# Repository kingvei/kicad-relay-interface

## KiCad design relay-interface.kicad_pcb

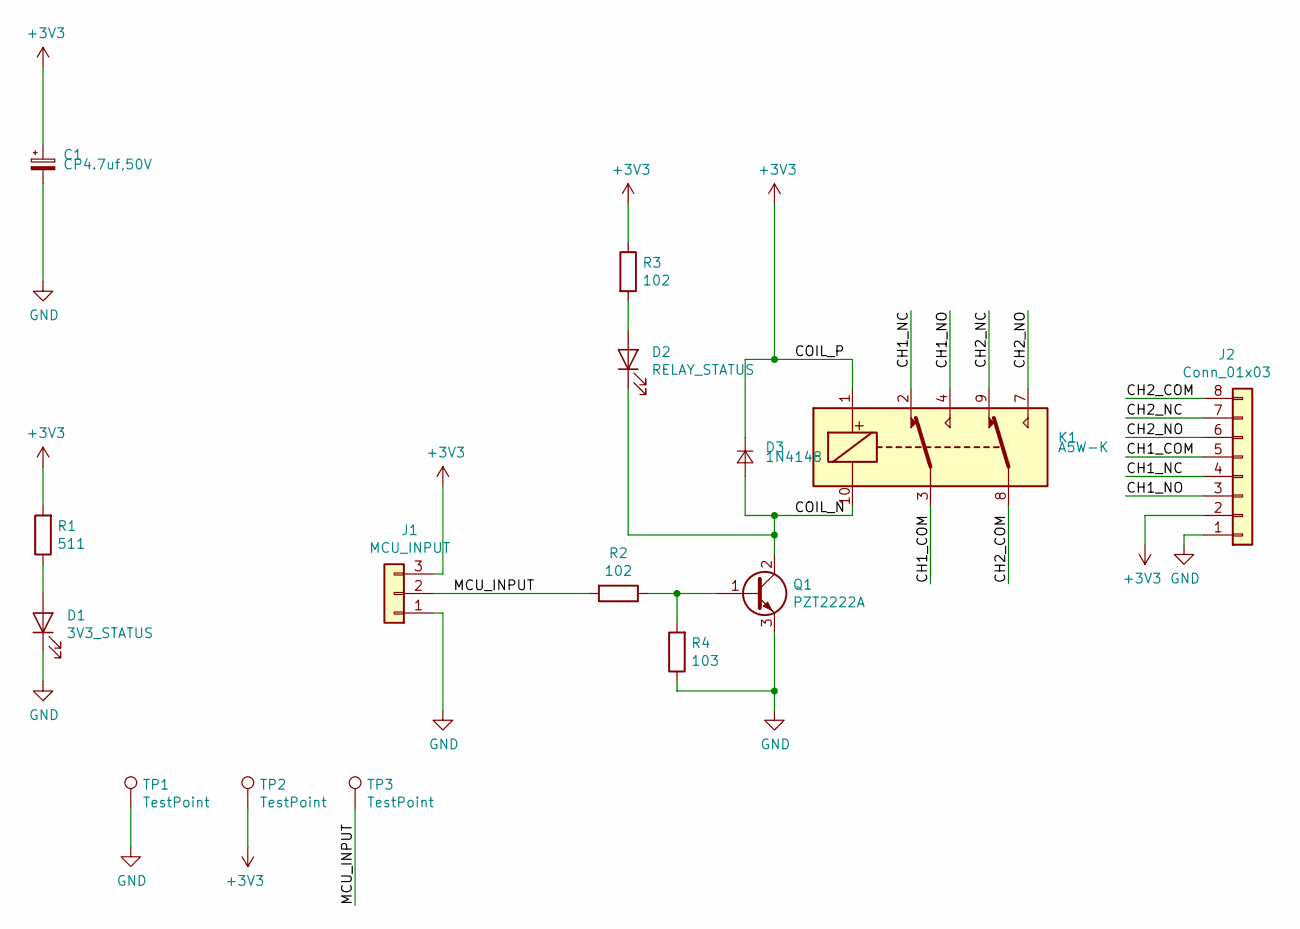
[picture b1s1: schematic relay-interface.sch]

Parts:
C1: CP4.7uf,50V; CP_Elec_4x5.3
D1: 3V3_STATUS; LED_0805_2012Metric_Castellated
D2: RELAY_STATUS; LED_0805_2012Metric_Castellated
D3: 1N4148; D_SOD-323_HandSoldering
J1: MCU_INPUT; PinHeader_1x03_P2.54mm_Vertical
J2: Conn_01x03; KF141V141R_Straight_1x08_Pitch2.54mm
K1: A5W-K; DIP-10_W7.62mm_LongPads
Q1: PZT2222A; SOT-223
R1: 511; R_0805_2012Metric_Pad1.15x1.40mm_HandSolder
R2, R3: 102; R_0805_2012Metric_Pad1.15x1.40mm_HandSolder
R4: 103; R_0805_2012Metric_Pad1.15x1.40mm_HandSolder
TP1, TP2, TP3: TestPoint; TestPoint_Pad_D2.0mm

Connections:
+3V3: C1.1, D3.1 (K), J1.3, J2.2, K1.1, R1.2, R3.1, TP2.1
/CH1_COM: J2.5, K1.3
/CH1_NC: J2.4, K1.2
/CH1_NO: J2.3, K1.4
/CH2_COM: J2.8, K1.8
/CH2_NC: J2.7, K1.9
/CH2_NO: J2.6, K1.7
/COIL_N: D2.1 (K), D3.2 (A), K1.10, Q1.2 (C)
/MCU_INPUT: J1.2, R2.2, TP3.1
GND: C1.2, D1.1 (K), J1.1, J2.1, Q1.3 (E), R4.1, TP1.1
unnamed: D1.2 (A), R1.1
unnamed: D2.2 (A), R3.2
unnamed: Q1.1 (B), R2.1, R4.2

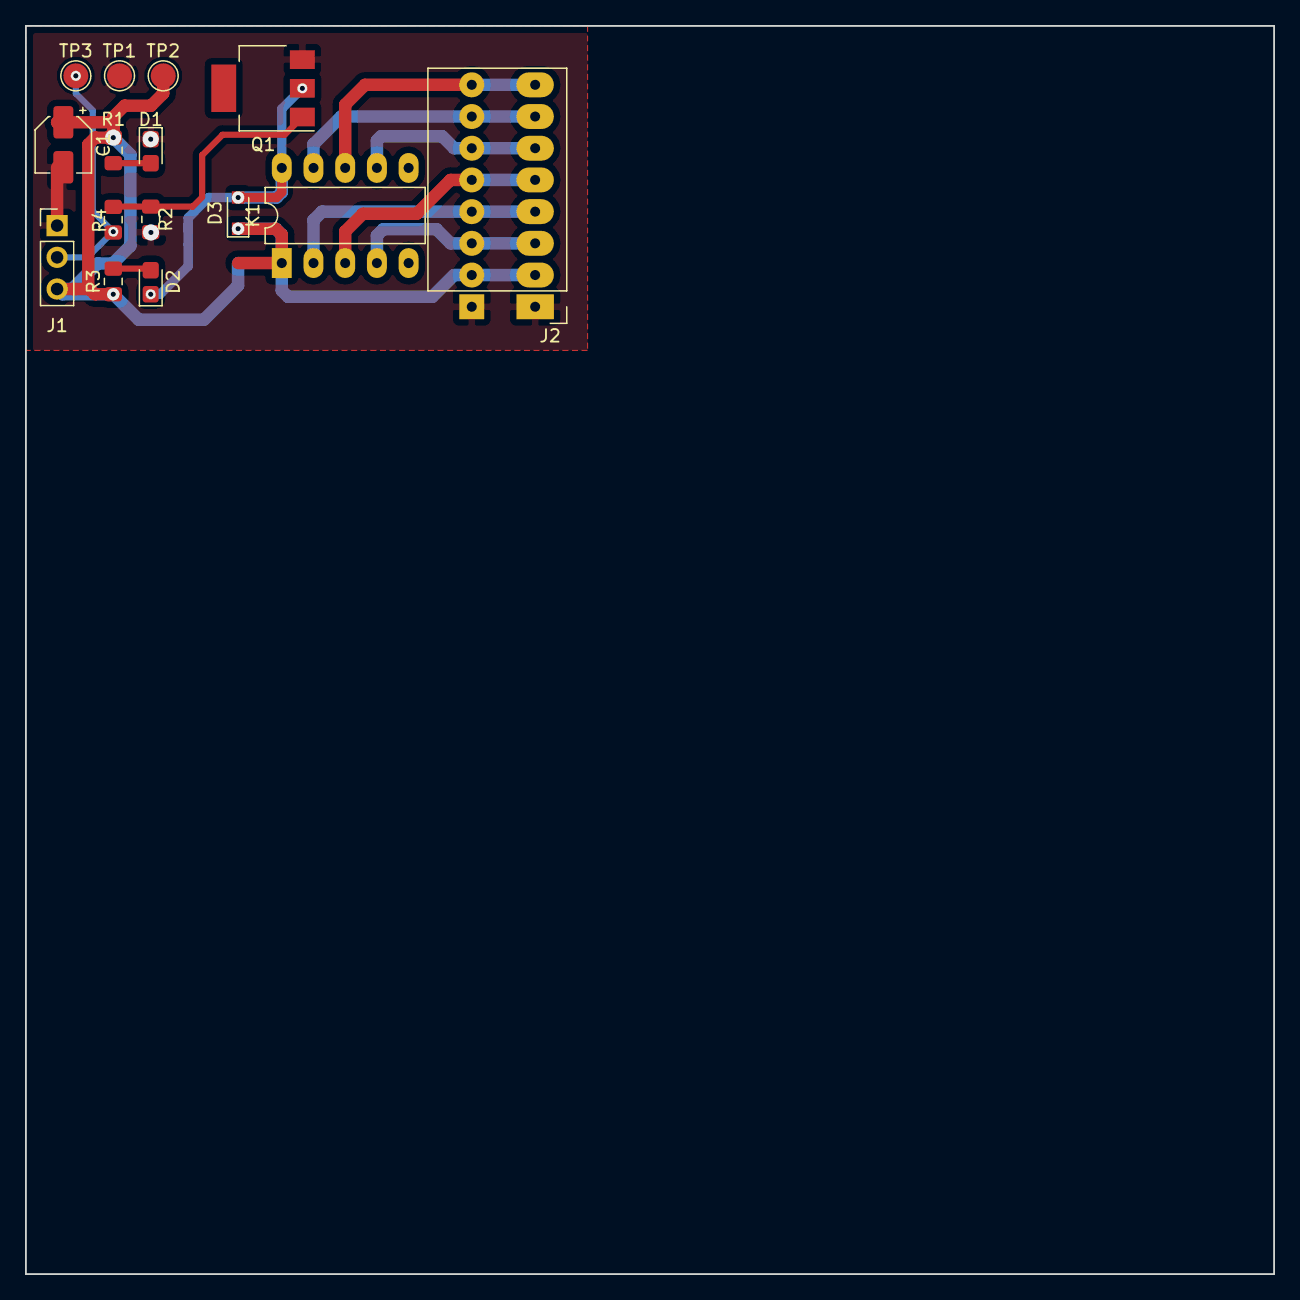
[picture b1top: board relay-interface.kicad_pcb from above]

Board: 2 copper layers, 100.0 x 100.0 mm, 15 parts (0 on the bottom side), 13 nets.

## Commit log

2020-05-12 init commit,
2020-05-12 add file and test,
2020-05-12 add datasheet and test,
2020-05-12 add kicad files and test,
